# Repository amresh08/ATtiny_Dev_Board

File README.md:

A Custom Developement Board Using The ATtiny85 Microcontroller for low cost and smaller applications

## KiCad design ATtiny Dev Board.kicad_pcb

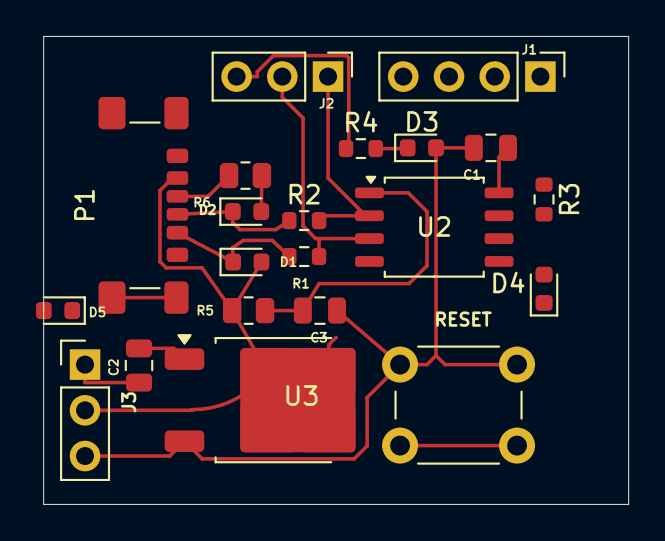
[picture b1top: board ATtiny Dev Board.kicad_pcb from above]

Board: 2 copper layers, 32.5 x 26.0 mm, 21 parts (0 on the bottom side), 17 nets.

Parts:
C1, C3: 0.1uF; C_0805_2012Metric
C2: 10uF; C_0805_2012Metric
D1, D2: 3.6V; D_0603_1608Metric
D3: LED; LED_0603_1608Metric
D4: ONBOARD BLUE LED; LED_0603_1608Metric
D5: D_Schottky; D_0603_1608Metric
J1: Conn_01x04; PinHeader_1x04_P2.54mm_Vertical
J2, J3: Conn_01x03; PinHeader_1x03_P2.54mm_Vertical
P1: USB_C_Plug_USB2.0; USB_C_Receptacle_GCT_USB4135-GF-A_6P_TopMnt_Horizontal
R1, R2: 68R; R_0603_1608Metric
R3: 330R; R_0603_1608Metric
R4: 220R; R_0603_1608Metric
R5: 10kR; R_0805_2012Metric
R6: 5.1kR; R_0805_2012Metric
SW1: RESET; SW_PUSH_6mm_H4.3mm
U2: ATtiny85-20S; SOIC-8_5.275x5.275mm_P1.27mm
U3: MC78M05_TO252; TO-252-2

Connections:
/5V: C1.2, C3.2, D3.2 (A), J3.3, SW1.2, U3.3 (VO)
/B9: D1.2 (A), D2.2 (A), D4.1 (K), J1.4, J2.3, J3.2, P1.S1 (SHIELD), R4.1, R5.2, R6.2, U2.4 (GND), U3.2 (GND)
/Vin: C2.2, J3.1
unnamed: D1.1 (K), P1.A6 (D+), R1.1
unnamed: D2.1 (K), P1.A7 (D-), R2.1
unnamed: D3.1 (K), R4.2
unnamed: D4.2 (A), R3.2
unnamed: D5.2 (A), P1.B5 (VCONN)
unnamed: C2.1, D5.1 (K), U3.1 (VI)
unnamed: J1.1, R3.1, U2.5 (AREF/PB0)
unnamed: J1.2, U2.6 (PB1)
unnamed: J1.3, U2.7 (PB2)
unnamed: J2.1, R2.2, U2.2 (XTAL1/PB3)
unnamed: J2.2, R1.2, U2.3 (XTAL2/PB4)
unnamed: P1.A5 (CC), R6.1
unnamed: C1.1, U2.8 (VCC)
unnamed: C3.1, R5.1, SW1.1, U2.1 (~RESET/PB5)

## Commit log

2025-02-05 README.md
